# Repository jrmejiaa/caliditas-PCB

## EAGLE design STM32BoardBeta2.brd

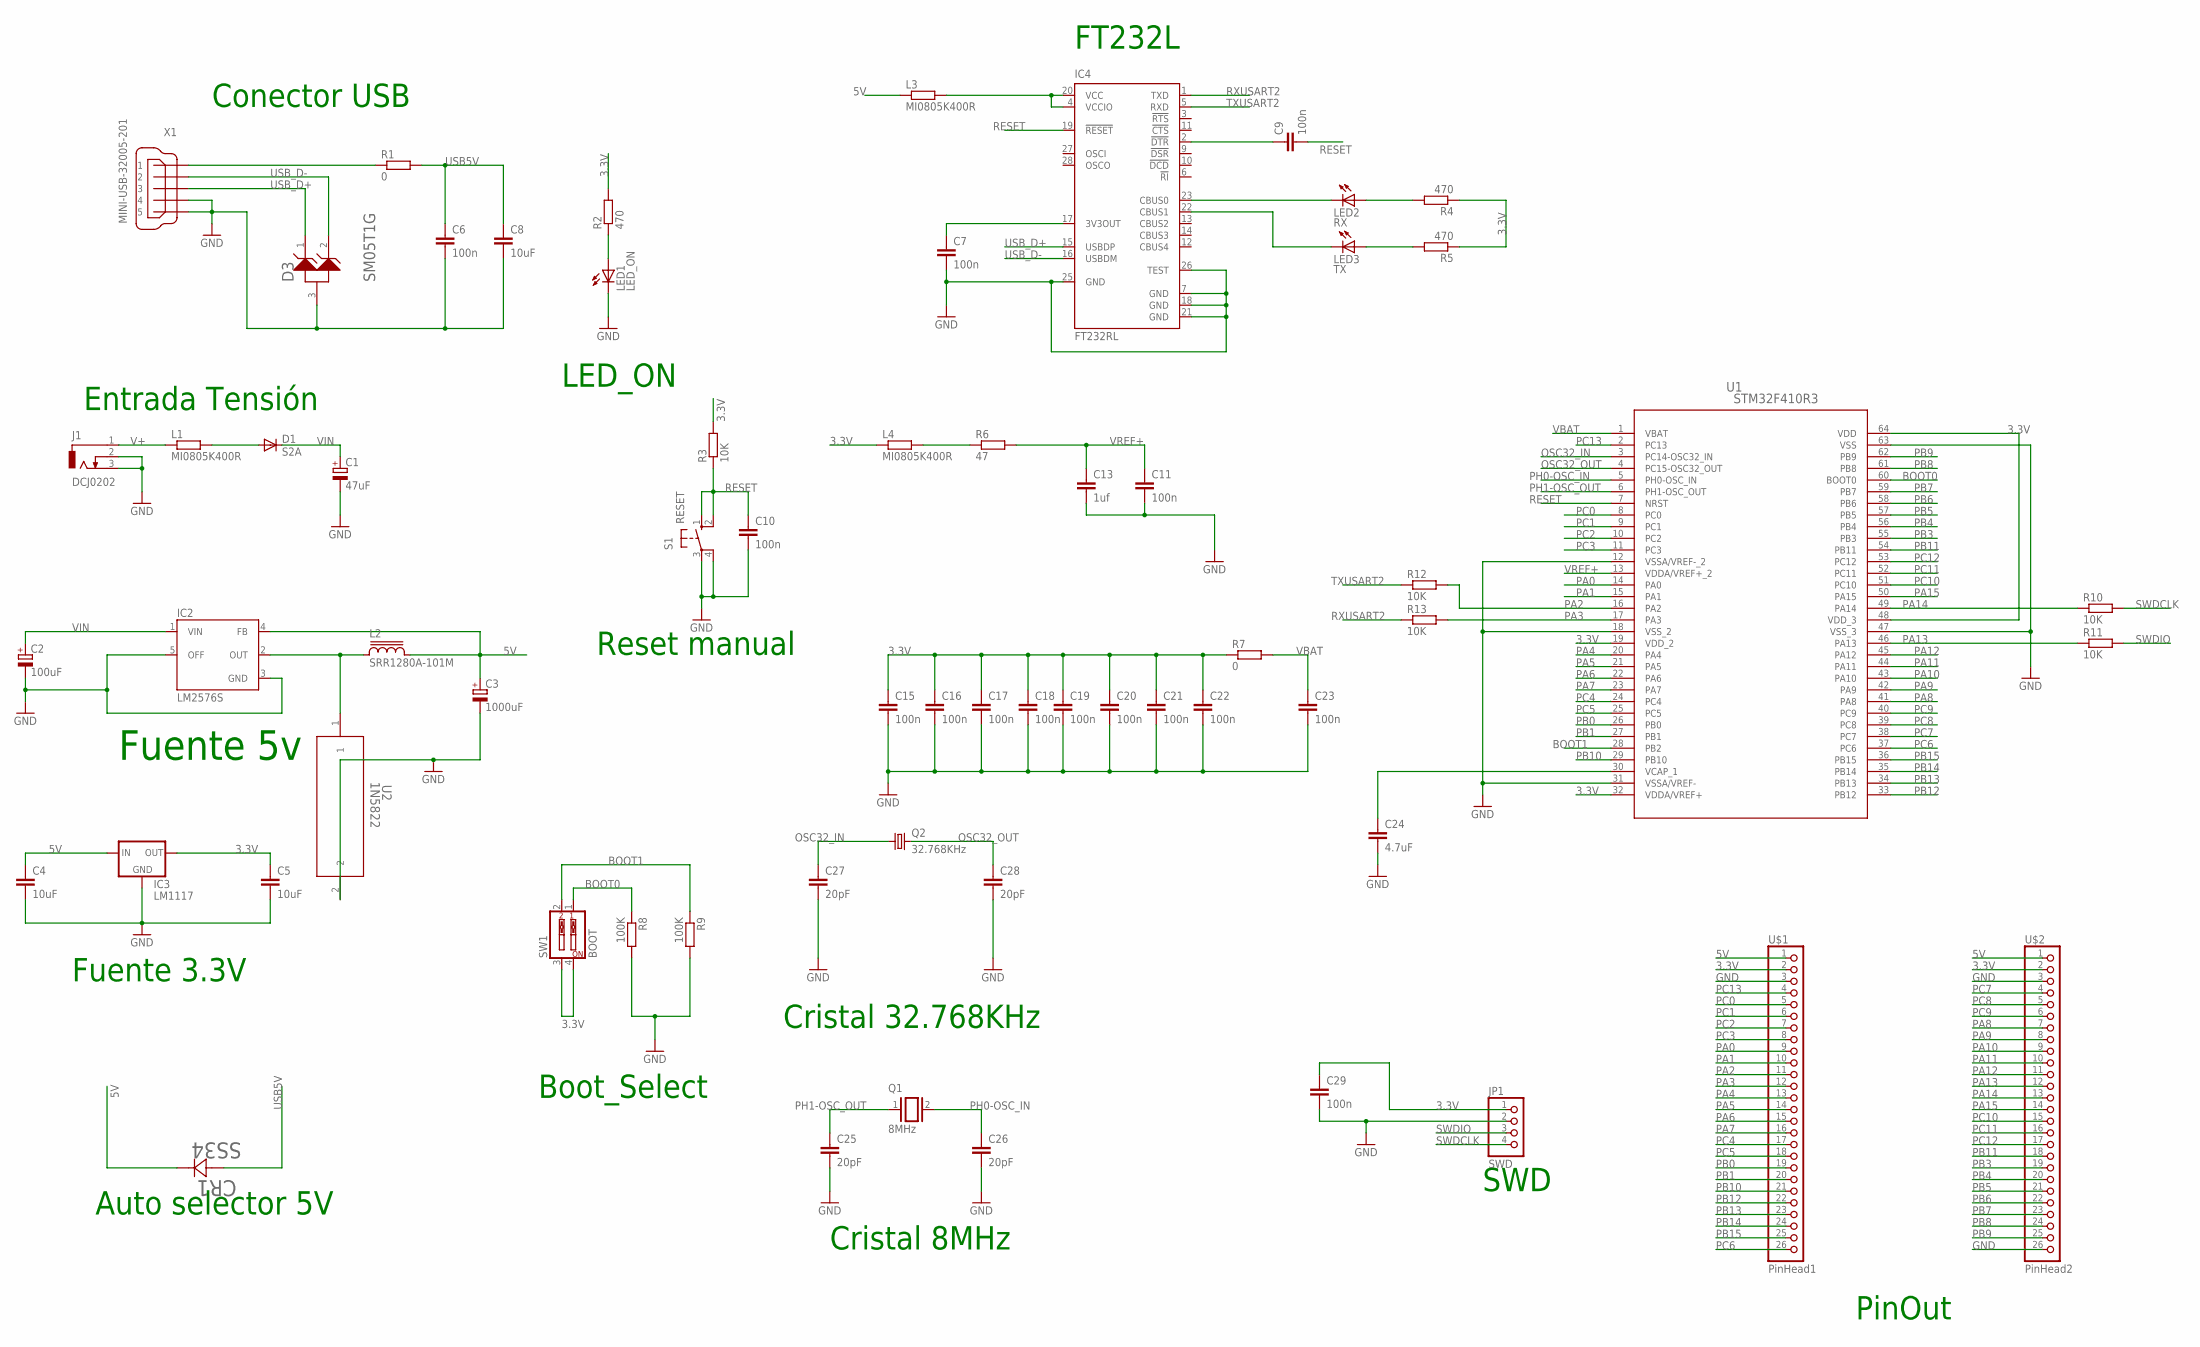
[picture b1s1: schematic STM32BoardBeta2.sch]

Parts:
C1: 47uF; 153CLV-0605
C2: 100uF; 153CLV-0605
C3: 1000uF; E5-10,5
C4, C5, C8: 10uF; C1206K
C6, C7, C9, C10, C11, C15, C16, C17, C18, C19, C20, C21, C22, C23, C29: 100n; C0805K
C13: 1uf; C0603
C24: 4.7uF; C1206K
C25, C26, C27, C28: 20pF; C0805K
CR1: SS34; DIODE_DO214AB-M
D1: S2A; DO214AA
D3: ON_SEMICONDUCTOR_SM05T1GON_SEMICONDUCTOR_SM05T1G_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; ON_SEMICONDUCTOR_SM05T1G_0
IC2: LM2576S; TO263-5
IC3: LM1117; TO252
IC4: FT232RL; SSOP28
J1: DCJ0202
JP1: SWD; 1X04
L1, L3, L4: MI0805K400R; M0805
L2: SRR1280A-101M; SRR1280
LED1: LED_ON; CHIP-LED0805
LED2: RX; CHIP-LED0805
LED3: TX; CHIP-LED0805
Q1: 8MHz; QS
Q2: 32.768KHz; TC26V
R1, R7: 0; M1206
R2, R4, R5: 470; R0805
R3: 10K; R1206
R6: 47; R0402
R8, R9: 100K; R0805
R10, R11, R12, R13: 10K; R0805
S1: RESET; B3F-10XX
SW1: BOOT; EDG-02
U1: STM32F410R3; LQFP64-10X10MM
U2: 1N5822; CASE_267-05
U$1: PinHead1; 1X26
U$2: PinHead2; 1X26
X1: MINI-USB-32005-201; 32005-201

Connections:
3.3V: C5.1, C15.1, C16.1, C17.1, C18.1, C19.1, C20.1, C21.1, C22.1, C29.1, IC3.TAB (OUT), JP1.1, L4.1, R2.2, R3.2, R4.1, R5.1, R7.1, SW1.3, SW1.4, U1.19 (VDD_2), U1.32 (VDDA/VREF+), U1.48 (VDD_3), U1.64 (VDD), U$1.2, U$2.2
5V: C3.+, C4.1, CR1.1, IC2.4 (FB), IC3.2 (IN), L2.2, L3.1, U$1.1, U$2.1
BOOT0: R8.1, SW1.1, U1.60 (BOOT0)
BOOT1: R9.1, SW1.2, U1.28 (PB2)
GND: C1.-, C2.-, C3.-, C4.2, C5.2, C6.2, C7.2, C8.2, C10.2, C11.2, C13.2, C15.2, C16.2, C17.2, C18.2, C19.2, C20.2, C21.2, C22.2, C23.2, C24.2, C25.2, C26.2, C27.2, C28.2, C29.2, D3.3 (A), IC2.3 (GND), IC2.5 (OFF), IC3.1 (GND), IC4.7 (GND), IC4.18 (GND), IC4.21 (GND), IC4.25 (GND), IC4.26 (TEST), J1.2, J1.3, JP1.2, LED1.C, R8.2, R9.2, S1.3, S1.4 (P1), U1.12 (VSSA/VREF-_2), U1.18 (VSS_2), U1.31 (VSSA/VREF-), U1.47 (VSS_3), U1.63 (VSS), U2.2, U$1.3, U$2.3, U$2.26, X1.4, X1.5
unnamed: LED1.A, R2.1
unnamed: IC4.4 (VCCIO), IC4.20 (VCC), L3.2
unnamed: D1.A, L1.2
unnamed: IC2.2 (OUT), L2.1, U2.1
unnamed: C7.1, IC4.17 (3V3OUT)
unnamed: R1.1, X1.1
unnamed: IC4.23 (CBUS0), LED2.C
unnamed: C9.1, IC4.2 (!DTR)
unnamed: IC4.22 (CBUS1), LED3.C
unnamed: LED2.A, R4.2
unnamed: LED3.A, R5.2
unnamed: C24.1, U1.30 (VCAP_1)
OSC32_IN: C27.1, Q2.1, U1.3 (PC14-OSC32_IN)
OSC32_OUT: C28.1, Q2.2, U1.4 (PC15-OSC32_OUT)
PA0: U1.14 (PA0), U$1.9
PA1: U1.15 (PA1), U$1.10
PA2: R12.2, U1.16 (PA2), U$1.11
PA3: R13.2, U1.17 (PA3), U$1.12
PA4: U1.20 (PA4), U$1.13
PA5: U1.21 (PA5), U$1.14
PA6: U1.22 (PA6), U$1.15
PA7: U1.23 (PA7), U$1.16
PA8: U1.41 (PA8), U$2.7
PA9: U1.42 (PA9), U$2.8
PA10: U1.43 (PA10), U$2.9
PA11: U1.44 (PA11), U$2.10
PA12: U1.45 (PA12), U$2.11
PA13: R11.1, U1.46 (PA13), U$2.12
PA14: R10.1, U1.49 (PA14), U$2.13
PA15: U1.50 (PA15), U$2.14
PB0: U1.26 (PB0), U$1.19
PB1: U1.27 (PB1), U$1.20
PB3: U1.55 (PB3), U$2.19
PB4: U1.56 (PB4), U$2.20
PB5: U1.57 (PB5), U$2.21
PB6: U1.58 (PB6), U$2.22
PB7: U1.59 (PB7), U$2.23
PB8: U1.61 (PB8), U$2.24
PB9: U1.62 (PB9), U$2.25
PB10: U1.29 (PB10), U$1.21
PB11: U1.54 (PB11), U$2.18
PB12: U1.33 (PB12), U$1.22
PB13: U1.34 (PB13), U$1.23
PB14: U1.35 (PB14), U$1.24
PB15: U1.36 (PB15), U$1.25
PC0: U1.8 (PC0), U$1.5
PC1: U1.9 (PC1), U$1.6
PC2: U1.10 (PC2), U$1.7
PC3: U1.11 (PC3), U$1.8
PC4: U1.24 (PC4), U$1.17
PC5: U1.25 (PC5), U$1.18
PC6: U1.37 (PC6), U$1.26
PC7: U1.38 (PC7), U$2.4
PC8: U1.39 (PC8), U$2.5
PC9: U1.40 (PC9), U$2.6
PC10: U1.51 (PC10), U$2.15
PC11: U1.52 (PC11), U$2.16
PC12: U1.53 (PC12), U$2.17
PC13: U1.2 (PC13), U$1.4
PH0-OSC_IN: C26.1, Q1.2, U1.5 (PH0-OSC_IN)
PH1-OSC_OUT: C25.1, Q1.1, U1.6 (PH1-OSC_OUT)
RESET: C9.2, C10.1, IC4.19 (!RESET), R3.1, S1.1 (S), S1.2 (S1), U1.7 (NRST)
RXUSART2: IC4.1 (TXD), R13.1
SWDCLK: JP1.4, R10.2
SWDIO: JP1.3, R11.2
TXUSART2: IC4.5 (RXD), R12.1
USB5V: C6.1, C8.1, CR1.2, R1.2
USB_D+: D3.1 (K1), IC4.15 (USBDP), X1.3
USB_D-: D3.2 (K2), IC4.16 (USBDM), X1.2
V+: J1.1, L1.1
VBAT: C23.1, R7.2, U1.1 (VBAT)
VIN: C1.+, C2.+, D1.C, IC2.1 (VIN)
VREF+: C11.1, C13.1, R6.2, U1.13 (VDDA/VREF+_2)
VREF+2: L4.2, R6.1

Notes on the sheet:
Fuente 5v
Entrada Tensión
Fuente 3.3V
Conector USB
Auto selector 5V
LED_ON
FT232L
Reset manual
Cristal 8MHz
Cristal 32.768KHz
Boot_Select
SWD
PinOut

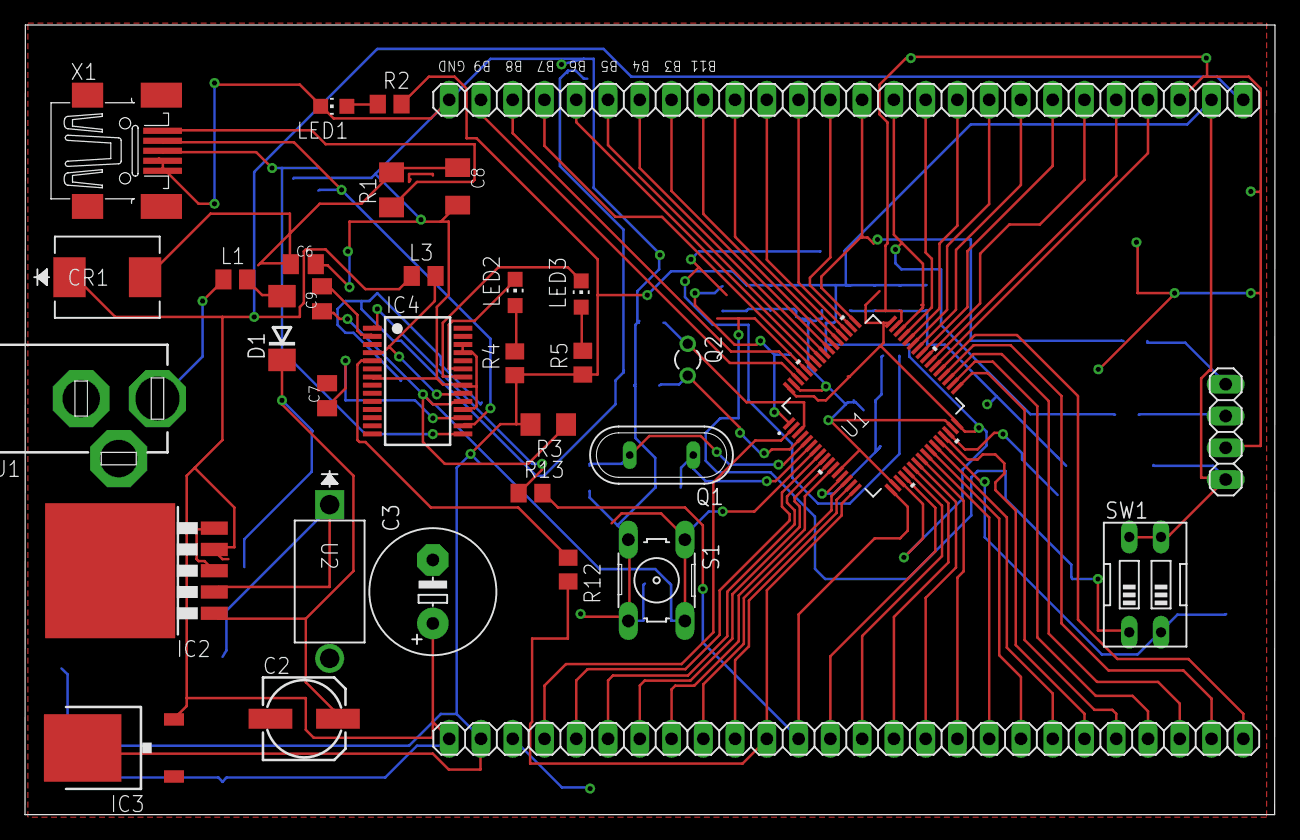
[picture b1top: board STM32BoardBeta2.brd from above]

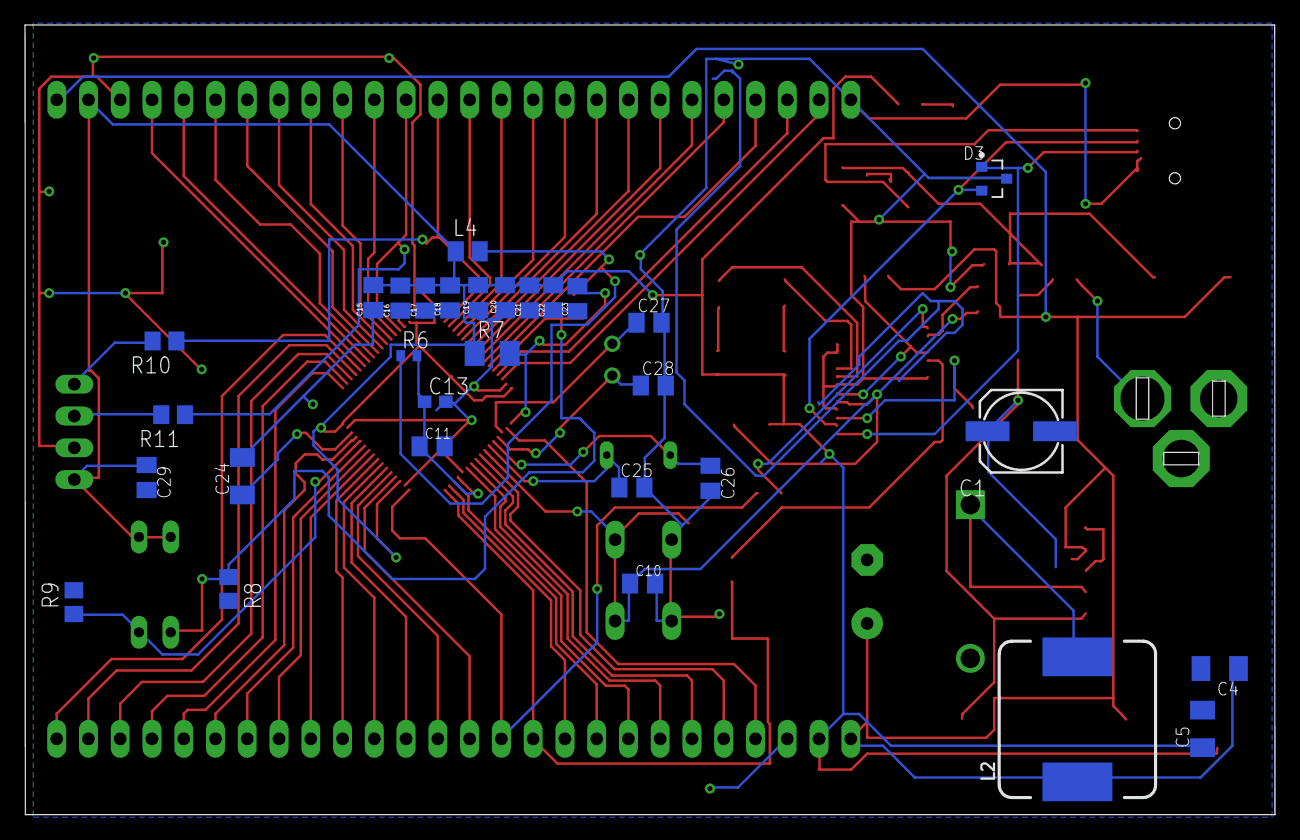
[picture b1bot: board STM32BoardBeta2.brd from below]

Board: 2 copper layers, 100.0 x 63.1 mm, 64 parts (30 on the bottom side), 79 nets.

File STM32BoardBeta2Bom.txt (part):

Partlist exported from /home/proyectos/eagle/STM32BoardBeta2/STM32BoardBeta2.sch at 18/12/18 15:06

Part Value                                                Device                                               Package                    Description                                                             COMPONENT_LINK_1_DESCRIPTION COMPONENT_LINK_1_URL   COMPONENT_LINK_3_DESCRIPTION COMPONENT_LINK_3_URL                                DATASHEET                                              DATASHEET_VERSION DIRECTION      IMPORTED IMPORTED_FROM IMPORT_TS  IR_MAX_UA MANUFACTURER_PART_NUMBER MF               MOUNTING_TECHNOLOGY MPN      OC_FARNELL OC_NEWARK PACKAGE         PACKAGE_DESCRIPTION                                               PACKAGE_VERSION  PACKING       PPK_MAX_W PREFIX ROHS VAULT_GUID                           VAULT_REVISION                       VENDOR            
C1   47uF                                                 CPOL-EU153CLV-0605                                   153CLV-0605                POLARIZED CAPACITOR, European symbol                                                                                                                                                                                                                                                                                                                                                                                                                                                                                                                                                                                                                                            
C2   100uF                                                CPOL-EU153CLV-0605                                   153CLV-0605                POLARIZED CAPACITOR, European symbol                                                                                                                                                                                                                                                                                                                                                                                                                                                                                                                                                                                                                                            
C3   1000uF                                               CPOL-EUE7.5-18                                       E7,5-18                    POLARIZED CAPACITOR, European symbol                                                                                                                                                                                                                                                                                                                                                                                                                                                                                                                                                                                                                                            
C4   10uF                                                 C-EUC1206K                                           C1206K                     CAPACITOR, European symbol                                                                                                                                                                                                                                                                                                                                                                                                                                                                                                                                                                                                                                                      
C5   10uF                                                 C-EUC1206K                                           C1206K                     CAPACITOR, European symbol                                                                                                                                                                                                                                                                                                                                                                                                                                                                                                                                                                                                                                                      
C6   100n                                                 C-EUC0805K                                           C0805K                     CAPACITOR, European symbol                                                                                                                                                                                                                                                                                                                                                                                                                                                                                                                                                                                                                                                      
C7   100n                                                 C-EUC0805K                                           C0805K                     CAPACITOR, European symbol                                                                                                                                                                                                                                                                                                                                                                                                                                                                                                                                                                                                                                                      
C8   10uF                                                 C-EUC1206K                                           C1206K                     CAPACITOR, European symbol                                                                                                                                                                                                                                                                                                                                                                                                                                                                                                                                                                                                                                                      
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
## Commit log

2019-04-08 Add files to EAGLE PCB Design
2019-04-09 Add Git Ignore file and change in the Schematic
2019-04-10 Cambios en condensador y diodo
2019-04-10 Actualización del diodo 1N5822, SS34 y cambio del tamaño del condensador
2019-04-10 Cambio en los condensadores 0201 a 0805

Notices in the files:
parts and their libraries:
inductor-bourns: Copyright (C) 2008, Bob Starr
